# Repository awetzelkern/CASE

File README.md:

# CASE
Miminal flight computer designed to be a stepping-stone into creating PCB hardware and software for a fully custom thrust-vectored rocket.

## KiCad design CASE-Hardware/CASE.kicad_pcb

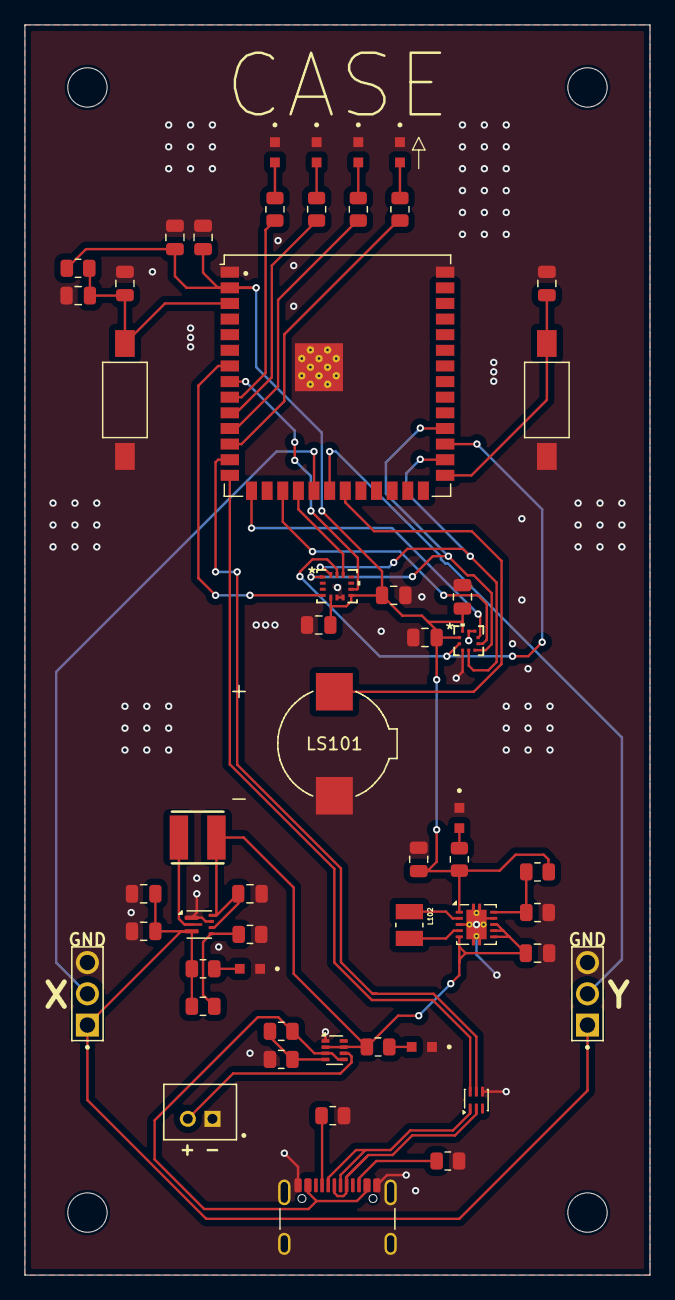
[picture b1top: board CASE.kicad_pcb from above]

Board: 2 copper layers, 50.8 x 101.6 mm, 57 parts (0 on the bottom side), 42 nets.

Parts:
C101, C103, C113: 0.1uF; C_0805_2012Metric
C102: 22uF; C_0805_2012Metric
C104, C105, C106, C107: 10uF; C_0805_2012Metric
C108: 47uF; C_0805_2012Metric
C109, C110, C111, C112: 100nF; C_0805_2012Metric
C114: 1uF; C_0805_2012Metric
D101: ORANGE LED; LED_APT1608SECK
D102: RED LED; LED_APT1608SECK
D103: YELLOW LED; LED_APT1608SECK
D104, D105, D106, D107: GREEN LED; LED_APT1608SECK
H101, H102, H103, H104: MountingHole; MountingHole_3.2mm_M3
J101: B2B-PH-K-S; JST_B2B-PH-K-S
J102: TVC_X; WURTH_61300311121
J103: TVC_Y; WURTH_61300311121
J104: USB_C_Receptacle_USB2.0_16P; USB_C_Receptacle_GCT_USB4105-xx-A_16P_TopMnt_Horizontal
L101: 1uH; WE-LQS_4025
L102: 1.5uH; INDC2520X100N
LS101: SMTB-0927-TW-R; XDCR_SMTB-0927-TW-R
R101, R102: 5.1k; R_0805_2012Metric
R104, R105, R106, R107, R114, R115, R116: 470; R_0805_2012Metric
R108, R111: 100k; R_0805_2012Metric
R109: 300k; R_0805_2012Metric
R110: 732k; R_0805_2012Metric
R112: 1M; R_0805_2012Metric
R113: 178k; R_0805_2012Metric
R128: 20k; R_0805_2012Metric
SW101, SW103: SW_Push; SW_SPST_FSMSM
U101: TPS61022; Texas_RWU0007A_VQFN-7_2x2mm_P0.5mm
U102: ECMF02-2AMX6; ST_UQFN-6L_1.5x1.7mm_P0.5mm
U103: ESP32-S3-WROOM-1U
U104: TPS2116DRL; SOT-583-8
U105: TPS63000; Texas_DRC0010J_ThermalVias
U106: BMI323; BMI323_BOS
U107: BMP581; QFN10_BMP581_BOS

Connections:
+3V3: C102.1, C103.1, C108.1, C109.1, C110.2, C111.1, C112.1, R112.1, R116.1, R128.2, U103.2 (3V3), U105.1 (VOUT), U106.5 (VDDIO), U106.8 (VDD), U107.1 (VDDIO), U107.10 (VDD)
+5V: C105.1, C106.1, J102.1, J103.1, R110.1, R115.1, U101.3 (VOUT)
/BAT_PWR: J101.2, U104.6 (VIN2)
/BMI_CS: U103.18 (IO10), U106.12 (CSB)
/BMI_INT1: U103.7 (IO7), U106.4 (INT1)
/BMI_INT2: U103.8 (IO15), U106.9 (INT2)
/BMP_CS: U103.17 (IO9), U107.6 (CSB)
/BMP_INT: U103.15 (IO3), U107.7 (INT)
/BOOT_SW: C113.2, SW101.1, U103.27 (IO0)
/BUZZER: LS101.P, U103.21 (IO13)
/LED_GREEN: R107.1, U103.9 (IO16)
/LED_ORANGE: R105.1, U103.12 (IO8)
/LED_RED: R104.1, U103.11 (IO18)
/LED_YELLOW: R106.1, U103.10 (IO17)
/MISO: U103.30 (IO37), U106.1 (SDO), U107.5 (SDO)
/MOSI: U103.28 (IO35), U106.14 (SDX), U107.4 (SDI)
/RAW_PWR: C104.1, C107.1, L101.1, R114.1, U101.5 (EN), U101.7 (VIN), U104.2 (VOUT), U104.7 (VOUT), U105.5 (VIN), U105.6 (EN), U105.7 (PS/SYNC), U105.8 (VINA)
/RESET_SW: C101.2, C114.1, R128.1, SW103.1, U103.3 (EN)
/SCK: U103.29 (IO36), U106.13 (SCX), U107.2 (SCK)
/TVC_X: J102.2, U103.19 (IO11)
/TVC_Y: J103.2, U103.20 (IO12)
/USB_D+: U102.6 (D+_out), U103.14 (IO20)
/USB_D-: U102.5 (D-_out), U103.13 (IO19)
/USB_PWR: J104.A4 (VBUS), J104.A9 (VBUS), J104.B4 (VBUS), J104.B9 (VBUS), R109.1, U104.3 (VIN1), U104.5 (MODE)
GND: C101.1, C102.2, C103.2, C104.2, C105.2, C106.2, C107.2, C108.2, C109.2, C110.1, C111.2, C112.2, C113.1, C114.2, D101.1, D102.1, D103.1, D104.1, D105.1, D106.1, D107.1, J101.1, J102.3, J103.3, J104.A1 (GND), J104.A12 (GND), J104.B1 (GND), J104.B12 (GND), J104.S1 (SHIELD), LS101.N, R101.2, R102.2, R108.2, R111.2, R113.2, SW101.2, SW103.2, U101.1 (GND), U101.6 (MODE), U102.4 (NC), U103.1 (GND), U103.40 (GND), U103.41 (EPAD), U104.1 (GND), U105.3 (PGND), U105.9 (GND), U105.11 (PGND), U106.6 (GNDIO), U106.7 (GND), U107.3 (VSS), U107.8 (VSS), U107.9 (VSS)
unnamed: D101.2, R105.2
unnamed: D102.2, R104.2
unnamed: D103.2, R106.2
unnamed: D104.2, R107.2
unnamed: D105.2, R114.2
unnamed: D106.2, R115.2
unnamed: D107.2, R116.2
unnamed: J104.A5 (CC1), R101.1
unnamed: J104.B5 (CC2), R102.1
unnamed: R110.2, R111.1, U101.4 (FB)
unnamed: L101.2, U101.2 (SW)
unnamed: J104.A7 (D-), J104.B7 (D-), U102.1 (D+_in)
unnamed: J104.A6 (D+), J104.B6 (D+), U102.2 (D-_in)
unnamed: R108.1, R109.2, U104.4 (PR1)
unnamed: R112.2, R113.1, U105.10 (FB)
unnamed: L102.2, U105.4 (L1)
unnamed: L102.1, U105.2 (L2)

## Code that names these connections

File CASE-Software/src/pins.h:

#pragma once
// when this file is included by more than one c file, it won't get copied more than one time

#define BMI_INT1    7
#define BMI_INT2    15

#define LED_GREEN   16
#define LED_YELLOW  17
#define LED_RED     18
#define LED_ORANGE  8

#define USB_D_MINUS 19
#define USB_D_PLUS  20

#define BMP_INT     3
#define BMP_CS      9
#define BMI_CS      10

#define TVC_X       11
#define TVC_Y       12

#define BUZZER      13

#define MISO        37
#define SCK         36
#define MOSI        35

#define BOOT_SW     0

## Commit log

2026-03-05 Added kicad files
2026-03-05 Added software folder
2026-03-11 Updated libraries for sensors to support BMI323 and BMP581
2026-03-11 Added LED functionality to indicate system success/failure
2026-03-13 Added note on mistake in wiring the ECMF02-2AMX6
2026-03-13 Added reference schematics for voltage regulators from Power Designer
2026-03-27 Added sensor functions, tested servo functionality
2026-03-27 Added notes to mistakes in schematic
2026-03-30 Began designing atmospheric model
